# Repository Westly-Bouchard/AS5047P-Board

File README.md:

Big thanks to [PCBWay](https://www.pcbway.com/) for sponsoring this project! Their support enables me (and hundreds of other designers) to make cool stuff. More info in [Manufacturing](#manufacturing)
<div align="center">

</div>
<br>
<p>
This is a breakout pcb for the commonly used AS5047P magnetic position sensor IC. Its SPI communication protocols are supported by many motor drivers such as VESCs and ODrives (newer ODrives have them built in, but boards based on the older open source designs like the ODesc don't). I designed this in KiCad, so if you want to work on it you'll need to install that.

It's also designed to mount easily with generic 360kv 5010 brushless motors like [these](https://speedyfpv.com/collections/brushless-motors/products/5010-brushless-motor-360kv-2-6s-high-torque-motor-for-14-18-props?variant=42912725860566). The mounting hole placement is sketched in an image below. There are two sets of holes, the wider set are 19mm apart and the closer set are 16mm apart.

This board exposes all possible communication interfaces with the IC:
- SPI
- ABI
- UVW
- PWM

Although it should be noted that some of these modes may require additional configuration over SPI to work (I believe the UVW mode needs to know the number of poles on the motor to function properly). Refer to the [datasheet](https://look.ams-osram.com/m/d05ee39221f9857/original/AS5047P-DS000324.pdf) for more information.

This board allows for either 3.3 or 5 volt operation through a solder jumper on the back side, and all of the connectors are JST GH (kits for these are easily available on amazon).

## Manufacturing
All of the files needed to manufacture these boards are provided in the `fabrication` folder.

The process is super easy if you use PCBWay:
1. Upload the `gerber.zip` file to their [instant quote tool](https://www.pcbway.com/QuickOrderOnline.aspx)
    * The default quantity is 5pcs, if you want more, change that here
    * This is a great opportunity to pick a specific color if you want something other than green
    * You may also want to select the `HASL lead free` option rather than the default leaded one
2. You can get bare boards, but assembling them yourself can be a pain. Fortunately, PCBWay can assemble them for you!
    1. Check the `Assembly Service` box. The default options are fine here, make sure to set the quantity of boards you want assembled.
    2. You can now hit the `Save to Cart` button on the right hand side of the screen.
    3. You'll be taken to the orders page, where you'll have to upload a couple more files.
    4. Hit the `Add File` button and upload the `Bom.csv` and `Centroid.csv` files
    5. Now the engineers at PCBWay have to review the order to ensure that everything is correct
    6. Once this process is compete, you can check out, and production will start

PCBWay's amazing customer service team will email you with updates and to check things like component placement throughout the process. But, these boards are fairly simple and there should be no issues here. You can also check the exact status of your order at any time on the website.

> ✅ Results
> 
> I am certainly biased, but I've found that PCBWay is easily the best way to get PCBs made. The quality of the silkscreen and accuracy of component placement are great. And, the constant updates & communications from the PCBWay team give me great confidence that my projects will succeed on the first try.
>
> I highly recommend their services. And, by supporting them, you support small projects and independent designers like myself!
<hr>

When it's all said and done, these cost me about $10 per board with shipping and tariffs included (I live in the US). If you choose the cheaper shipping option and don't have to deal with crazy tariffs, then these could get down closer to $7 per board, which is a fantastic deal. Especially considering that similar encoders like the AS5048A on amazon cost closer to $14 per board (at least at the time of writing).

If you find a mistake, or want to make an improvement, feel free to open a pr!

Mounting hole spacing, the holes are M3.
</p>
<div align="center">
  
</div>

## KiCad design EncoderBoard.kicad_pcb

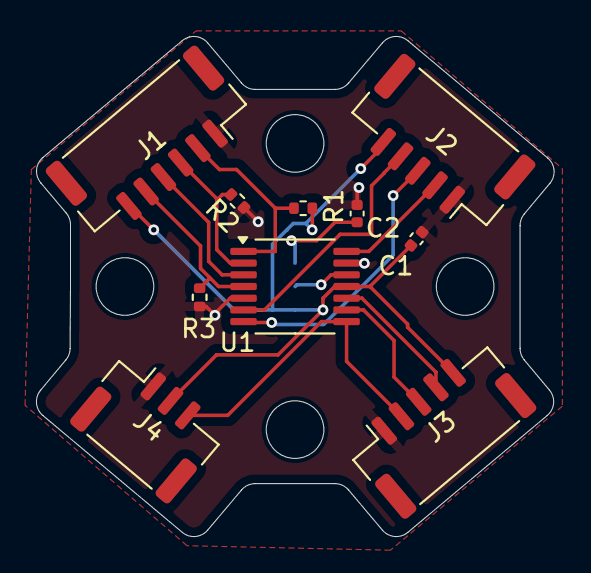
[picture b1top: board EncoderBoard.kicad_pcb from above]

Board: 2 copper layers, 28.8 x 27.8 mm, 15 parts (1 on the bottom side), 14 nets.

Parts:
C1: 100nF; C_0402_1005Metric
C2: 1uF; C_0402_1005Metric
H1, H2, H3, H4: MountingHole; MountingHole_3.2mm_M3
J1: Conn_01x06_MountingPin; JST_GH_SM06B-GHS-TB_1x06-1MP_P1.25mm_Horizontal
J2, J3: Conn_01x05_MountingPin; JST_GH_SM05B-GHS-TB_1x05-1MP_P1.25mm_Horizontal
J4: Conn_01x03_MountingPin; JST_GH_SM03B-GHS-TB_1x03-1MP_P1.25mm_Horizontal
JP1: SolderJumper_3_Bridged12; SolderJumper-3_P1.3mm_Open_RoundedPad1.0x1.5mm
R1, R2, R3: 10k; R_0402_1005Metric
U1: AS5047P; TSSOP-14_4.4x5mm_P0.65mm

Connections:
GND: C1.2, C2.2, J1.1, J2.1, J3.1, J4.1, R2.1, R3.1, U1.5 (TST), U1.13 (GND)
unnamed: J1.2, R1.2, U1.1 (~CS)
unnamed: J1.3, R2.2, U1.2 (CLK)
unnamed: J1.4, U1.3 (MISO)
unnamed: J1.5, R3.2, U1.4 (MOSI)
unnamed: J2.2, U1.14 (I/PWM)
unnamed: J2.3, U1.7 (A)
unnamed: J2.4, U1.6 (B)
unnamed: J3.2, J4.3, U1.8 (W/PWM)
unnamed: J3.3, U1.9 (V)
unnamed: J3.4, U1.10 (U)
unnamed: C2.1, JP1.1 (A)
unnamed: JP1.2 (C), U1.12 (VDD3V3)
VDD: C1.1, J1.6, J2.5, J3.5, J4.2, JP1.3 (B), R1.1, U1.11 (VDD)

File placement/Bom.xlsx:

Comment | Designator | Footprint | JLCPCB Part #
100nF | C1 | C_0402_1005Metric | C1525
1uF | C2 | C_0402_1005Metric | C52923
JST GH SM06 | J1 | JST_GH_SM06B-GHS-TB_1x06-1MP_P1.25mm_Horizontal | C133065
JST GH SM05 | J2,J3 | JST_GH_SM05B-GHS-TB_1x05-1MP_P1.25mm_Horizontal | C189896
JST GH SM03 | J4 | JST_GH_SM03B-GHS-TB_1x03-1MP_P1.25mm_Horizontal | C514175
AS5047P | U1 | Package_SO:TSSOP-14_4.4x5mm_P0.65mm | C962063
10kOhm | R1,R2,R3 | R_0402_1005Metric | C25744

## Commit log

2025-07-26 Add readme
2025-08-09 Update for V2
2025-08-18 Add step file
2025-08-22 Add gitignore
2025-08-22 Remove cached files
2025-08-22 Update gitignore
2025-08-22 Remove more stuff
2025-08-22 Remove .DS_Store
2025-08-23 Restructuring
2025-08-23 Add fabrication files
2025-12-21 Update with PCBWay shout-out
2025-12-21 Small grammar changes
2026-02-08 Add CERN Open Hardware Licence Version 2
    Added CERN Open Hardware Licence Version 2 - Weakly Reciprocal to the project.
2026-02-08 Updates to readme
2026-02-08 Improve image layout in README.md
    Updated image alignment and sizes in README.
2026-02-08 Update recommendation wording in README
    Rephrase biased statement to emphasize personal opinion.
